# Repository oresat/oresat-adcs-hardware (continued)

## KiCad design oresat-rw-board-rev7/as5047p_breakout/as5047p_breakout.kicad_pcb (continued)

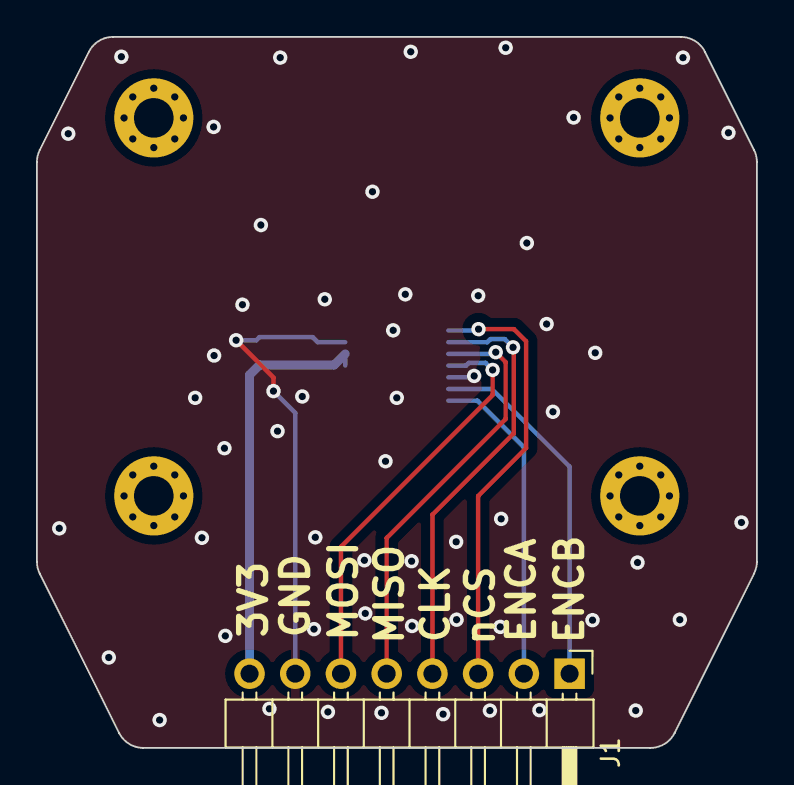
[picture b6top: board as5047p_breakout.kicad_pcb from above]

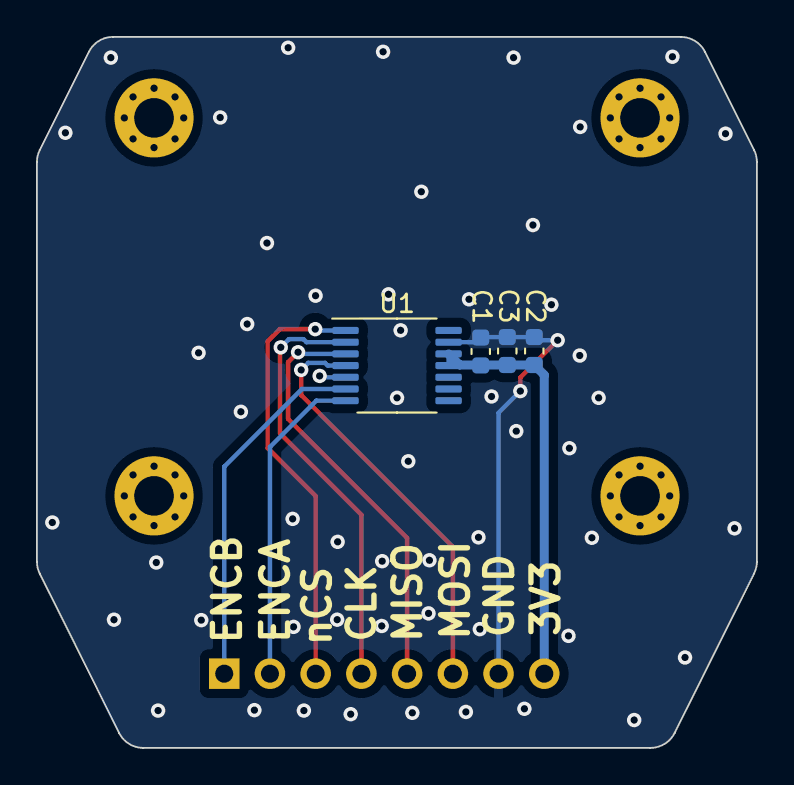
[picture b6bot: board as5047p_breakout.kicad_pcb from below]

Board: 2 copper layers, 40.0 x 39.5 mm, 6 parts (4 on the bottom side), 8 nets.

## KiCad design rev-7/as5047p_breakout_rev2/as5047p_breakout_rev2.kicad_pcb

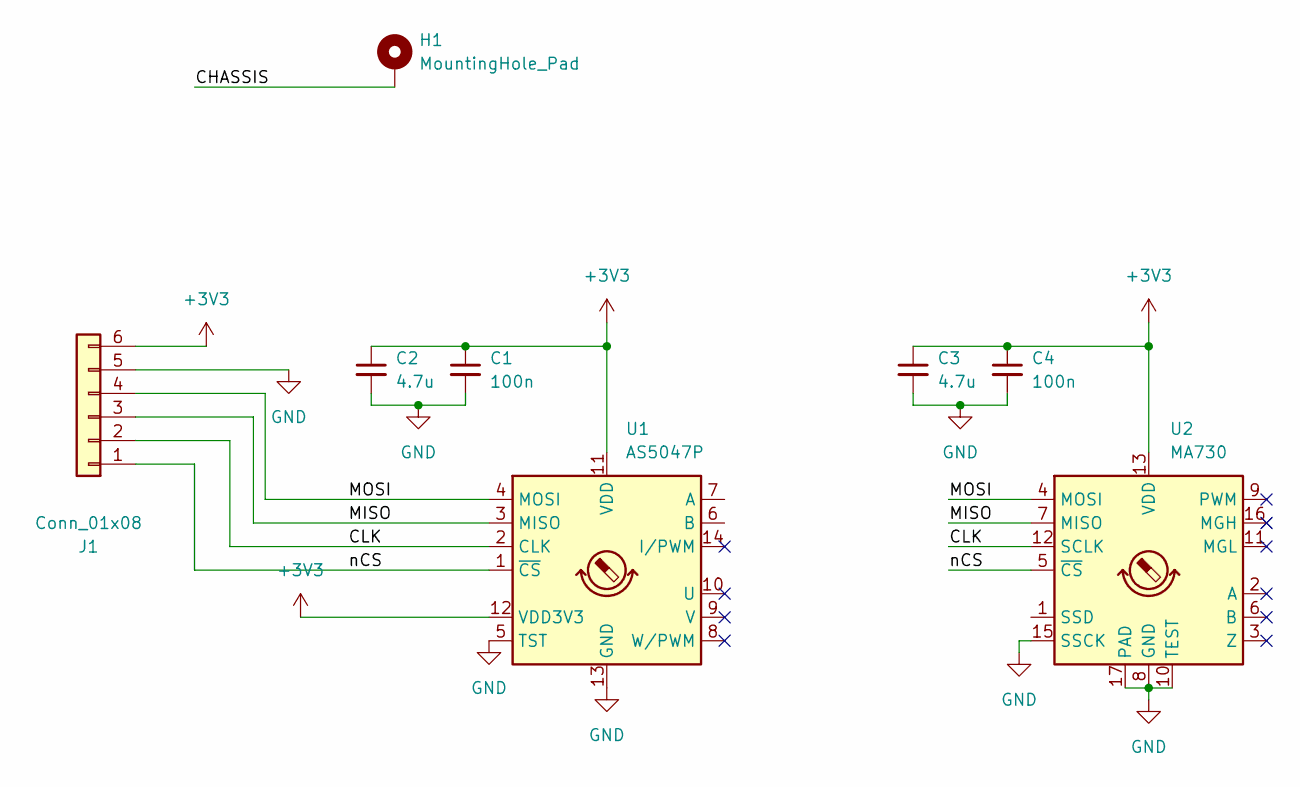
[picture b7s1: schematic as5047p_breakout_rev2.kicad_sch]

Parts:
C1, C4: 100n; C_0603_1608Metric
C2, C3: 4.7u; C_0603_1608Metric
H1: MountingHole_Pad; board-def-rev7.3
J1: Conn_01x08; PinHeader_1x06_P2.54mm_Horizontal
U1: AS5047P; TSSOP-14_4.4x5mm_P0.65mm
U2: MA730; QFN-16-1EP_3x3mm_P0.5mm_EP1.75x1.75mm

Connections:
+3V3: C1.1, C2.1, C3.1, C4.1, J1.6, U1.11 (VDD), U1.12 (VDD3V3), U2.13 (VDD)
/CHASSIS: H1.1
/CLK: J1.2, U1.2 (CLK), U2.12 (SCLK)
/MISO: J1.3, U1.3 (MISO), U2.7 (MISO)
/MOSI: J1.4, U1.4 (MOSI), U2.4 (MOSI)
/nCS: J1.1, U1.1 (~CS), U2.5 (~CS)
GND: C1.2, C2.2, C3.2, C4.2, J1.5, U1.5 (TST), U1.13 (GND), U2.8 (GND), U2.10 (TEST), U2.15 (SSCK), U2.17 (PAD)

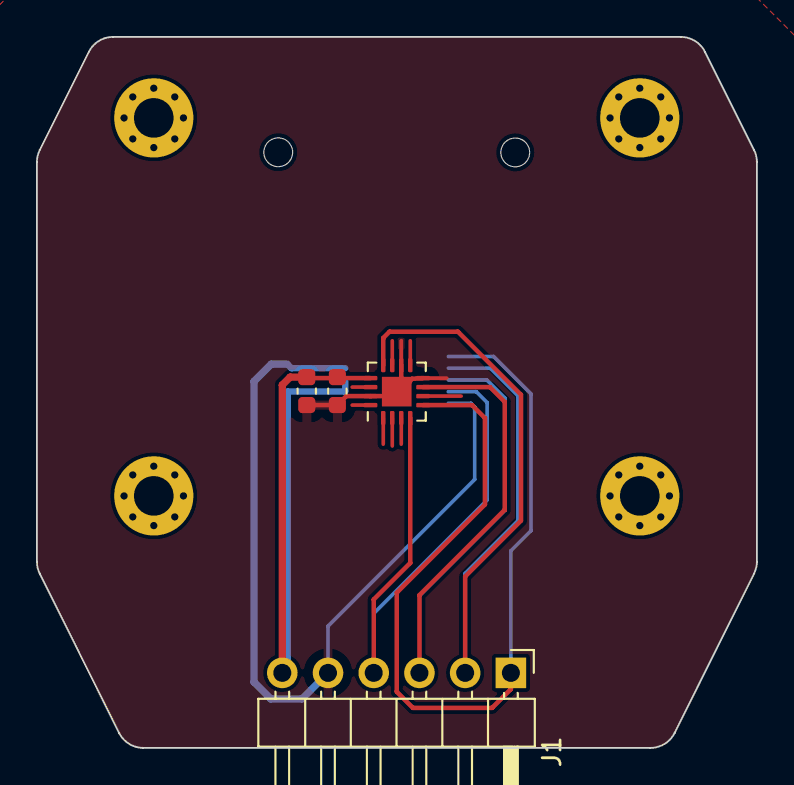
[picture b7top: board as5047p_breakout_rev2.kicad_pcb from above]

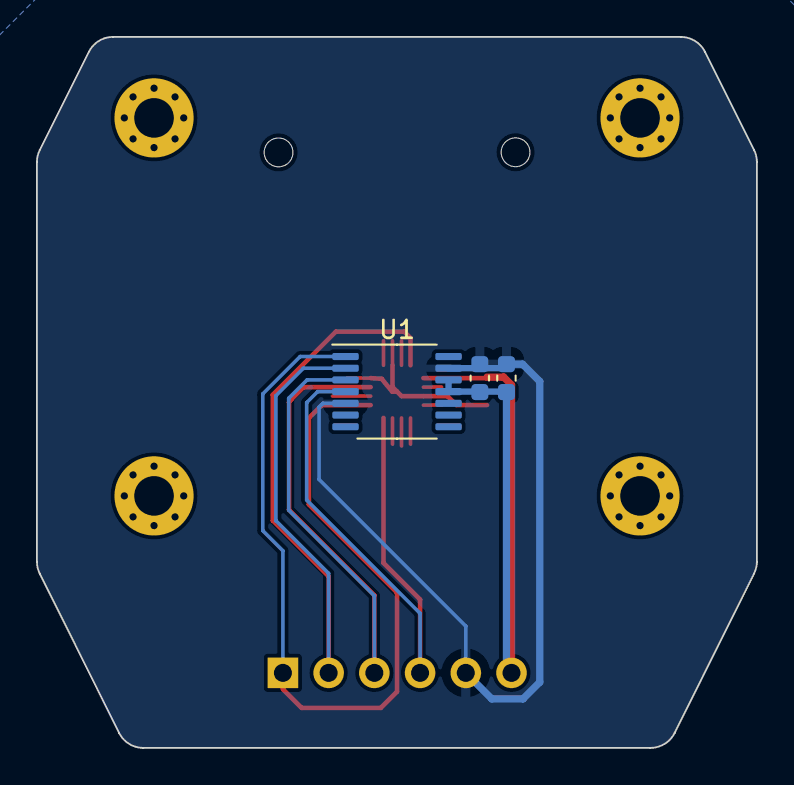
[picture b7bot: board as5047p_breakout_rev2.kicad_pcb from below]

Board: 2 copper layers, 40.0 x 39.5 mm, 8 parts (3 on the bottom side), 6 nets.

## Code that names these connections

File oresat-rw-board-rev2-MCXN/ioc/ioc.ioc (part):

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Mcu.Name=STM32G474V(B-C-E)Hx
Mcu.Package=TFBGA100
Mcu.UserName=STM32G474VEHx
PA0.GPIOParameters=GPIO_Label
PA0.GPIO_Label=PHA_I
PA0.Mode=IN1-Single-Ended
PA0.Signal=ADC1_IN1
PA1.GPIOParameters=GPIO_Label
PA1.GPIO_Label=PHC_I
PA1.Mode=IN2-Single-Ended
PA1.Signal=ADC2_IN2
PA10.GPIOParameters=GPIO_Label
PA10.GPIO_Label=PHB_H
PA10.Mode=Output_TB1TB2
PA10.Signal=HRTIM1_CHB1
PA11.GPIOParameters=GPIO_Label
PA11.GPIO_Label=PHB_L
PA11.Mode=Output_TB1TB2
PA11.Signal=HRTIM1_CHB2
PA13.Mode=Trace_Synchro_4bits_SW
PA13.Signal=SYS_JTMS-SWDIO
PA14.Mode=Trace_Synchro_4bits_SW
PA14.Signal=SYS_JTCK-SWCLK
PA15.GPIOParameters=GPIO_Label
PA15.GPIO_Label=SPI_nCS
PA15.Mode=NSS_Signal_Hard_Output
PA15.Signal=SPI3_NSS
PA2.GPIOParameters=GPIO_Label
PA2.GPIO_Label=PHA_V
PA2.Mode=IN3-Single-Ended
PA2.Signal=ADC1_IN3
PA4.GPIOParameters=GPIO_Label
PA4.GPIO_Label=DAC_1
PA4.Signal=COMP_DAC11_group
PA5.GPIOParameters=GPIO_Label
PA5.GPIO_Label=DAC_2
PA5.Signal=COMP_DAC12_group
PA6.Signal=COMP_DAC21_group
PA7.GPIOParameters=GPIO_Label
PA7.GPIO_Label=PHC_V
PA7.Mode=IN4-Single-Ended
PA7.Signal=ADC2_IN4
PA8.GPIOParameters=GPIO_Label
PA8.GPIO_Label=PHA_H
PA8.Mode=Output_TA1TA2
PA8.Signal=HRTIM1_CHA1
PA9.GPIOParameters=GPIO_Label
PA9.GPIO_Label=PHA_L
PA9.Mode=Output_TA1TA2
PA9.Signal=HRTIM1_CHA2
PB1.GPIOParameters=GPIO_Label
PB1.GPIO_Label=PHB_I
PB1.Mode=IN1-Single-Ended
PB1.Signal=ADC3_IN1
PB3.GPIOParameters=GPIO_Label
PB3.GPIO_Label=SWO
PB3.Signal=GPIO_Output
PB5.GPIOParameters=GPIO_Label
PB5.GPIO_Label=CAN_ADDR1
PB5.Signal=GPIO_Input
PB7.GPIOParameters=GPIO_Label
PB7.GPIO_Label=CAN_ADDR0
PB7.Signal=GPIO_Input
PB8-BOOT0.GPIOParameters=GPIO_Label
PB8-BOOT0.GPIO_Label=BOOT0
PB8-BOOT0.Signal=GPIO_Input
PC10.GPIOParameters=GPIO_Label
PC10.GPIO_Label=SPI_SCK
PC10.Mode=Full_Duplex_Master
PC10.Signal=SPI3_SCK
PC11.GPIOParameters=GPIO_Label
PC11.GPIO_Label=SPI_MISO
PC11.Mode=Full_Duplex_Master
PC11.Signal=SPI3_MISO
PC12.GPIOParameters=GPIO_Label
PC12.GPIO_Label=SPI_MOSI
PC12.Mode=Full_Duplex_Master
PC12.Signal=SPI3_MOSI
PC8.GPIOParameters=GPIO_Label
PC8.GPIO_Label=PHC_H
PC8.Mode=Output_TE1TE2
PC8.Signal=HRTIM1_CHE1
PC9.GPIOParameters=GPIO_Label
PC9.GPIO_Label=PHC_L
PC9.Mode=Output_TE1TE2
PC9.Signal=HRTIM1_CHE2
PD0.GPIOParameters=GPIO_Label
PD0.GPIO_Label=CAN_RX
PD0.Mode=FDCAN_Activate
PD0.Signal=FDCAN1_RX
PD1.GPIOParameters=GPIO_Label
PD1.GPIO_Label=CAN_TX
PD1.Mode=FDCAN_Activate
PD1.Signal=FDCAN1_TX
PD2.GPIOParameters=GPIO_Label
PD2.GPIO_Label=DEBUG1
PD2.Signal=GPIO_Output
PD3.GPIOParameters=GPIO_Label
PD3.GPIO_Label=DEBUG3
PD3.Signal=GPIO_Output
PD4.GPIOParameters=GPIO_Label
PD4.GPIO_Label=DEBUG0
PD4.Signal=GPIO_Output
PD5.GPIOParameters=GPIO_Label
PD5.GPIO_Label=DEBUG_TX
PD5.Mode=Asynchronous
PD5.Signal=USART2_TX
PD6.GPIOParameters=GPIO_Label
PD6.GPIO_Label=DEBUG_RX
PD6.Mode=Asynchronous
PD6.Signal=USART2_RX
PD7.GPIOParameters=GPIO_Label
PD7.GPIO_Label=DEBUG2
PD7.Signal=GPIO_Output
PE0.GPIOParameters=GPIO_Label
PE0.GPIO_Label=DFU_TX
PE0.Mode=Asynchronous
PE0.Signal=USART1_TX
PE1.GPIOParameters=GPIO_Label
PE1.GPIO_Label=DFU_RX
PE1.Mode=Asynchronous
PE1.Signal=USART1_RX
PE10.GPIOParameters=GPIO_Label
PE10.GPIO_Label=THERM3
PE10.Mode=IN14-Single-Ended
PE10.Signal=ADC5_IN14
PE11.GPIOParameters=GPIO_Label
PE11.GPIO_Label=THERM2
PE11.Mode=IN15-Single-Ended
PE11.Signal=ADC5_IN15
PE12.GPIOParameters=GPIO_Label
PE12.GPIO_Label=THERM0
PE12.Mode=IN16-Single-Ended
PE12.Signal=ADC5_IN16
PE14.GPIOParameters=GPIO_Label
PE14.GPIO_Label=VBUS_V
PE14.Mode=IN1-Single-Ended
PE14.Signal=ADC4_IN1
PE2.Mode=Trace_Synchro_4bits_SW
PE2.Signal=SYS_TRACECLK
PE3.Mode=Trace_Synchro_4bits_SW
PE3.Signal=SYS_TRACED0
PE4.Mode=Trace_Synchro_4bits_SW
PE4.Signal=SYS_TRACED1
PE5.Mode=Trace_Synchro_4bits_SW
PE5.Signal=SYS_TRACED2
PE6.Mode=Trace_Synchro_4bits_SW
PE6.Signal=SYS_TRACED3
PE8.GPIOParameters=GPIO_Label
PE8.GPIO_Label=THERM1
PE8.Mode=IN6-Single-Ended
PE8.Signal=ADC5_IN6
PE9.GPIOParameters=GPIO_Label
PE9.GPIO_Label=PHB_V
PE9.Mode=IN2-Single-Ended
PE9.Signal=ADC3_IN2
PF0-OSC_IN.Mode=HSE-External-Oscillator
PF0-OSC_IN.Signal=RCC_OSC_IN
PF1-OSC_OUT.Mode=HSE-External-Oscillator
PF1-OSC_OUT.Signal=RCC_OSC_OUT
PG10-NRST.GPIOParameters=GPIO_Label
PG10-NRST.GPIO_Label=nRST
PG10-NRST.Signal=GPIO_Input
RCC.HSE_VALUE=8000000
RCC.SYSCLKFreq_VALUE=144000000
RCC.SYSCLKSource=RCC_SYSCLKSOURCE_PLLCLK
board=custom

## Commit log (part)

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2018-02-22 Cosmetic fixes: Added labels. All resistors and capacitors are numbered. Updated the symbol of the encoder. Updated the symbol and package of the STSPIN230. Boxed LEDs and placed a note "NP FOR FLIGH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
2018-02-23 Added a testpoint to the CAN transciever.
2018-02-24 Nice job, Nathan! Did a bit of visual polish, updated AMS symbol to be more compact. Big changes: Added new TPS63070 SPS circuit from solar board, redid LEDs on magnetorquer. BLDC LEDs should be that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
2018-02-24 Checked all ERC. Looks good. Eric go ahead and start board layout again.
2018-02-26 Resized component packages for power considerations and for package size consistency.
2018-02-26 Layout Start
    Start organization of board layout
2018-03-02 finished power/started BLDC d
2018-03-02 add Q-out/ more on layout
    Quadrature output has been added to the schematic for Josh to collect data from motor spec test.
2018-03-04 Nealy dere
2018-03-06 Board Rev1
2018-03-10 Here's what I have for the BOM.
2018-03-13 Board to send out
2018-03-19 First revision of a hardware guide which describes all the hardware components in the motor controller schematic. There are a couple of components I wasn't sure about. This document needs a little mo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
2018-03-30 Schematic PDFs
2018-03-30 Updated PDF
2018-04-27 [WIP] restore from workstation @E-Ruhl
2018-05-11 rev2 LFD
2018-05-12 part placement on rev3
2018-05-13 rev 3 progress
2018-05-15 rev3 needs design review
2018-05-15 Rev 3 Ready for final sendout (Don't forget the stencils)
2018-05-15 last change, I'm pretty sure
2018-05-21 Clean up from last week: added three test points because test points are important when you might need a signal, and added signal names because N names are dumb, and cleaned up a few ERC warnings. An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
2018-05-22 Manufacturing photos looks like OSHpark boards. These photos are good for documentation and presentation.
2018-05-22 Schematic photos for documentation
2018-05-23 rev2
2018-05-24 poster picture
2018-05-24 poster print
    touched up pad overlap
2018-06-05 Images of schematic files for both Rev1.1 and Rev3.
2018-06-05 Created a PDF of Rev 3 schematic.
2018-06-15 For some reason the previous PDF only had page 1. I fixed it now.
2018-06-16 Formatting the readme with block diagram photos.
2018-06-16 Adding block diagram to readme
2018-06-16 Adding level 2 block diagram to readme
2018-06-16 Adding info on block diagram systems.
2018-06-16 Made a project requirements document as markdown.
2018-06-16 Fixed some formatting mistakes.
2018-06-16 Changed name to make more sense.
2018-06-16 Fixed table formatting.
2018-06-17 Added schematic photos to readme
2018-06-17 I'm bad at formatting...
2018-06-17 *sign* I have to push every few changes to make sure I'm doing this correctly...
2018-06-17 Adding the capstone poster to the readme file.
2018-06-17 Changed the hardware reference guide from a word file to a markdown file.
2018-06-17 Added research references in markdown format.
2018-06-17 Added Research references and bibliography.md
2018-06-17 deleting PDF folder
2018-06-18 Updated readme and added SOP for board stuffing.
2018-06-18 comp
2018-06-18 Adding readme file and new folder
    folder ACS Capstone
2018-06-18 Update Readme.md
    Testing to see if images show after changes.
2018-06-18 Update Readme.md
    Adding schematic photos
2018-06-18 Update Readme.md
    Adding the rest of the pictures
2018-06-18 Add photos
2018-06-18 Update Ramp Up
2018-06-18 adding important files
2018-06-18 adding correct system diagram
2018-06-18 system diagram png
2019-03-04 f4 updates
2019-06-25 L4 updates
2019-06-28 Prelim final rev completed + design overhaul
2019-06-29 archived
2019-06-30 Post review updates
2019-07-10 reorganization
2019-07-10 schematic updates for Hardware reference guide
2019-07-10 Hardware updates
2019-07-11 start of 4.1 and OreSat card
2019-07-16 Current set of modifications for Rev4.1 completed, some errors found and corrected
2019-07-16 Board images
2019-07-19 mods
2019-07-24 order update
2019-08-14 Placing extra circuit breakers for ACS card
2019-08-19 Oresat Card
2019-08-21 ACS card updates
2019-08-24 L4 pinout update
2019-08-31 Adding grant proposal and final report PDFs
    from OreSat Shared Drive
2019-09-07 Board connector update
2019-09-08 rev4.2 ready for review
2019-09-20 added quadrent marker resistors and tappered lower corners for more clearence
2019-09-24 layer 2 mod
2020-01-07 updated design block for card power system
2020-01-08 power domain updates
2020-01-14 ACS oresat standard card adapted for group routing
2020-01-27 Flex cable prototype
2020-01-27 file organizing
2020-01-27 mechanical outlines
2020-01-27 Final polish on v4.2b; sent off to OSH Park.
2020-01-29 Sanity check Eric's card. Removing supply symbols even though this is causing Andrew physical pain but EAGLE can't deal with renaming supply symbols. Also more text.
2020-06-26 Layed out power domains for four quadrants, added another power domain and an STM32F042. Also added breaker circuit and I2C buffer for Magnetometers, and an IMU
2020-06-30 Flattening rev4.3
2020-07-02 Reworked board layout to avoid space taken up by inhibit switches on battery board
2020-07-15 Cleaned up bNames layer, and added ground vias around board
2020-07-20 Floated BMI088 CSB2 because CSB1 was and data sheet said it had a pull up; switched to card outline with no RF connectors (whoops), moved ground stitching near edges to under TSTOP, fixed some DRC er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
2020-07-25 Added first version of acs card bom
2020-07-27 Flattening the board
2020-07-31 traces routed, still needs polygons and planes
2020-08-06 Board Flattened ready for review
2020-08-07 test point update for rev 4.3
2020-08-11 flat board ready for second round of inspection
2020-09-08 Doubled up MAG_SDA and MAG_SCL on backplane connector to match backplane, and added pull up resistors for these signals. Updated BOM to reflect this.
2020-09-21 Standardized passives to 0603 and changed all test points to circular footprint. Spaced out components in OPD for easier stuffing. Cleaned up names layer. Fixed OPD protection circuit to match OPD de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
2020-09-22 Fixed attributes and updated BOM. Also doubled up backplane connector lines and added some test points.
2020-09-23 Added flight marker
2020-09-23 Updated flight marker
2021-04-07 Create .~lock.oresat-acs-card-bom.xlsx#
2022-01-20 Rev 5.0
2022-02-07 Rev 6 pre design review
2022-02-07 Fixed ERC/DRC errors and design rules
2022-02-08 Fix DRC issues on power stage
2022-02-09 Added BoM, fixed footprints
2022-02-09 Remove temp file
2022-02-10 Added production files for ground split version
2022-02-10 Add nonsplit ground version
2022-04-03 Rev 7 power stage schematic complete
2022-04-04 Prelim power stage layout
2022-04-05 Add 3dmodels for TSON FET
2022-04-06 Design review changes
2022-05-10 Pushing changes to rev7
2022-06-30 Updated PCB layoud. Changed magnetorquer connection to 6 position pin terminal
2022-07-12 Updated 5V regulators to match design block. Added UART switch to microcontroller. Added power flags and cleaned up ERC errors
2022-07-19 Updated some attributes and resistor values to clean up BOM
2022-07-19 Beginning cleanup of the ADCS repo. Removing kicad and eaglecad and trying to make sense of all of this.
2022-07-19 Moved ACS card BOM into ACS card folder.
2022-07-19 Moved old documentation into archive and deleted some really really old stuff. Created a documentation folder.
2022-07-21 Updated card name. Now oresat-adcs-card instead of oresat-acs-card.
2022-07-22 Update README.md
    Better formatting, bring license up
2022-07-24 Updated inductor footprint
2022-08-18 Added ADCS card block diagram v1.0
2022-09-29 Updating
2022-10-07 Legacy rev6
2022-10-07 please do not touch my directory structure until this is in space
2022-10-12 Switch to running mag encoder on 3v3, move to OResat standard debug connector
2022-11-20 Added breakout board for RW mezzanine connector
2023-01-15 Extended mezzanine flex pcb so that we can slide the connector, and added silkscreen name
2023-02-13 Fixed ADCS card issues
2023-02-20 Fixed more ADCS card issues
2023-05-17 Quick commit pre-board changes
2023-05-28 Add v7.1
2023-06-07 Responding to review notes
2023-06-07 Fix clearances, fix silk, add vias
2023-06-12 Cleanup stitching on power stage, cleanup DRC control stage, add AS5047P breakout for wheel testingf
2023-07-20 Updated ADCS card and fixed library issues
2023-11-05 Push power stage rev 7.2 - production
2023-11-13 Updated date on silkscreen
2023-11-22 Changed sensor-power schematic filename to card-power
2023-11-27 Put build products (gerbers) in the build directory, and ignore archive and build directories in git.
2023-12-04 Remove old stencil files
2023-12-04 Unbreak symbol/fp libs
2024-02-25 changed mezanine flex board to shorten to 14.5mm down from 19mm
2024-02-26 CAM settings in PCB file.
2024-05-03 Remove some build files.
2024-05-03 Upgrade to KiCAD 8!
2024-05-19 Fixed missing component values
2025-09-28 New project directories for splitting up adcs card schematics
2025-11-09 Magnetorquer ADCS Board
    Magnetorquer and reaction wheel breakout; changed schematic to use hierarchy style labels instead of global net labels. Changed uC to MCXN from STM32. Changed backplane connector to OreSat 1 connecto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
2025-11-11 MCXN RW Control Board Revision 4
2025-11-23 Finished Schematic
    Added MCXN uC, new ICM-42688-P IMU, removed reaction wheels, reannotated schematics, etc.
2025-11-23 Removed temporary file
2025-11-24 Updated schematic symbols
    Updated schematic symbols to have yellow background and fixed a couple of local net labels
2025-12-15 Housekeeping items before board layout
    Changed capacitor to C_Small, changed transistor schematic symbols, moved C5 down to iC, changed 10k pull ups to 4.7k pull ups onto root page. Changed U10 and U9 so that they have the yellow backgrou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
2025-12-16 Schematic Update
    Updated schematic to fix all ERC violations and errors, removed all traces of old EAGLE imported components and replaced with either OreSat or Kicad native symbols and footprints.
2025-12-17 Updated schematic pin names and directions.
2025-12-19 Design review changes on schematic.
    Fixed UART lines, relabeled some OPD outputs from the MAX7310, fixed I2C pullups, lots of small polishing. Ready for layout.
2025-12-28 Pushed because Andrew told me to
2025-12-28 Rename to oresat-rw-card, which is what this is.
2026-01-01 RW card needs scrutiny
2026-01-07 Schematic Done + Board outline set
    Fixed heirarchical labels, cleaned up ERCs, board is ready for layout
2026-02-09 Push for design review
2026-02-20 Push for critiques
2026-02-22 Found a layout that works, barely, needs lots of cleanup!
2026-02-27 rough layout finished
2026-03-01 Mag card- Finished
    Completed PCB layout and routing.
2026-03-04 Commit because I was told to
    Also fixed a lot of things
2026-03-08 main connector done
2026-03-09 Silkscreen cleaned up
2026-03-09 Schematic and layout polishing and prep for fabrication
    Updated schematic symbols, cleaned up schematic pages to be more like protocard, removed uncessessary TPs, updated layout, cleaned up layout routing and some zones, added Makefile and READMEs for fab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
2026-03-10 Fixed a few small BOM issues, checked everything, ready for fab.
2026-03-12 Update
    Updated footprints, symbols, and pcb layout to have IMU in center of board.
2026-03-29 Final touch ups
    Added new j3 connector, and final touch ups
2026-03-30 Update before fab!
    Last final changes to pcb before fab: changed location of connector back to original. Changed silk screen to reflect date and mag board v1.0
2026-04-02 Sent off for fabrication.
    Last sweep of BOM, ground stitching, and inner layer planes. Lots of small tweaks.
2026-04-03 Fixed Footprint/Symbol Library Issue
2026-04-03 Formatted for *make* to work
2026-04-06 Fix BOM - some packages were wrong size, caught by CM.
2026-04-07 Final mag card
    Lots of polishing around best practices layout. Put in giant hole to thread the MTs from below if required for the 3U CubeSats. Cleaned up power layer, added stitching vias, updated readme.
2026-04-07 Remove old back side silkscreen
2026-04-08 Updated BOM part
2026-04-20 Updated keepout on MCXN RW board mezzanine connector and fixed kicad .gitignore for kicad 10
2026-04-20 RW Flex board for Mezzanine connectors v1.2
    This board is for RW board v8.0 and RW card v1.0. Note specialized Makefile for flex board including stiffeners.
2026-04-21 Updated Version on Board & Schematic
2026-05-07 Updated VSNS Resistor Values to Properly Reflect 3.0V ADC Reference
